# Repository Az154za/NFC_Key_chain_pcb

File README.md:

# NFC_Key_chain_pcb
Well this is key_chain_ncf_pcb powered by NT3H2111 in which you can add your linkdln profile or whatever link you want .
This project was made to make sharing your linkdln profile more fluent and easier for the user ( you can add a sticker to conver the pcb and make it more professional if wanted ) 
to do this Just Download the gerber files and print it then have fun 
# BOM :
| # | Component                            | Supplier   | Price | Delivery | Total    |
|---|--------------------------------------|------------|------------|----------|----------|
| 2 | PCB Manufacturing (2-layer)          | JLCPCB     | $37    | Included | $37   |
|   | https://jlcpcb.com                                                                      |
|---|--------------------------------------|------------|------------|----------|----------|
|   | GRAND TOTAL                          |            |            |          | $37   |
# Schematic :

# PCB :

# 3D overview :

# 3D model :

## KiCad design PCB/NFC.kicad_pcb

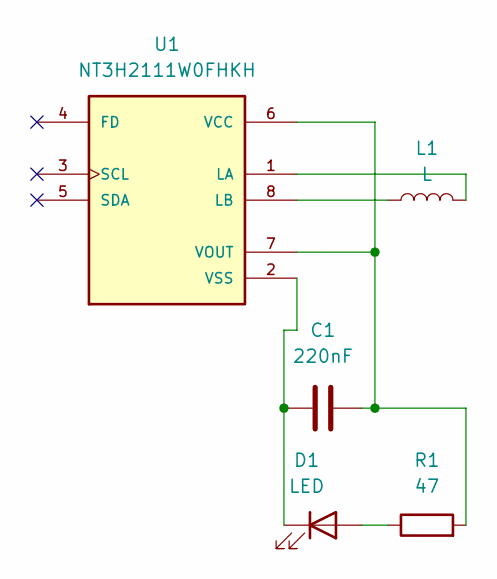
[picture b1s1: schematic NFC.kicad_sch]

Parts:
C1: 220nF; C_0402_1005Metric
D1: LED; LED_0402_1005Metric
L1: L; KiCadAntenna
R1: 47; R_0402_1005Metric
U1: NT3H2111W0FHKH; QFN8P50_160X160X50L40X20N

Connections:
unnamed: D1.2 (A), R1.1
unnamed: C1.1, D1.1 (K), U1.2 (VSS)
unnamed: L1.2, U1.1 (LA)
unnamed: L1.1, U1.8 (LB)
unnamed: C1.2, R1.2, U1.6 (VCC), U1.7 (VOUT)

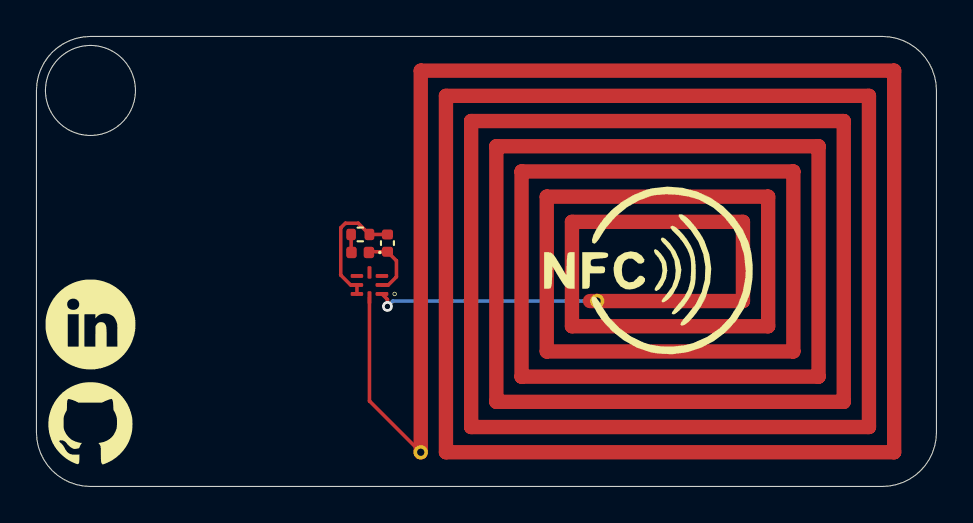
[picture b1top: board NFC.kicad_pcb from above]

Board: 2 copper layers, 50.0 x 25.0 mm, 5 parts (0 on the bottom side), 5 nets.

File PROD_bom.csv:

Designator,Footprint,Quantity,Value,LCSC Part #
C1,0402,1,220nF,
D1,0402,1,LED,
L1,KiCadAntenna,1,L,
R1,0402,1,47,
U1,QFN8P50_160X160X50L40X20N,1,NT3H2111W0FHKH,

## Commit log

2026-03-16 Replace PCB image with a new one
    Updated PCB image in README with a new source.
2026-03-16 Add PN532 NFC Reader/Writer implementation
    This file implements a PN532 NFC Reader/Writer for Raspberry Pi using I2C. It includes methods for initializing the device, reading and writing NFC tags, and handling MIFARE commands.
2026-05-11 Fix typo in README description
2026-05-11 Revise component prices in README.md
    Updated unit prices and grand total in the components table.
